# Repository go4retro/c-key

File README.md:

#Commodore PS/2 Keyboard Adapter

##License
Copyright (C) 2004 Jim Brain and RETRO Innovations

These files are free designs; you can redistribute them and/or modify
them under the terms of the GNU General Public License, version 2 as 
published by the Free Software Foundation.

These files are distributed in the hope that they will be useful,
but WITHOUT ANY WARRANTY; without even the implied warranty of
MERCHANTABILITY or FITNESS FOR A PARTICULAR PURPOSE.  See the
GNU General Public License for more details.

You should have received a copy of the GNU General Public License along
with these files; if not, write to the Free Software Foundation, Inc.,
51 Franklin Street, Fifth Floor, Boston, MA 02110-1301 USA.

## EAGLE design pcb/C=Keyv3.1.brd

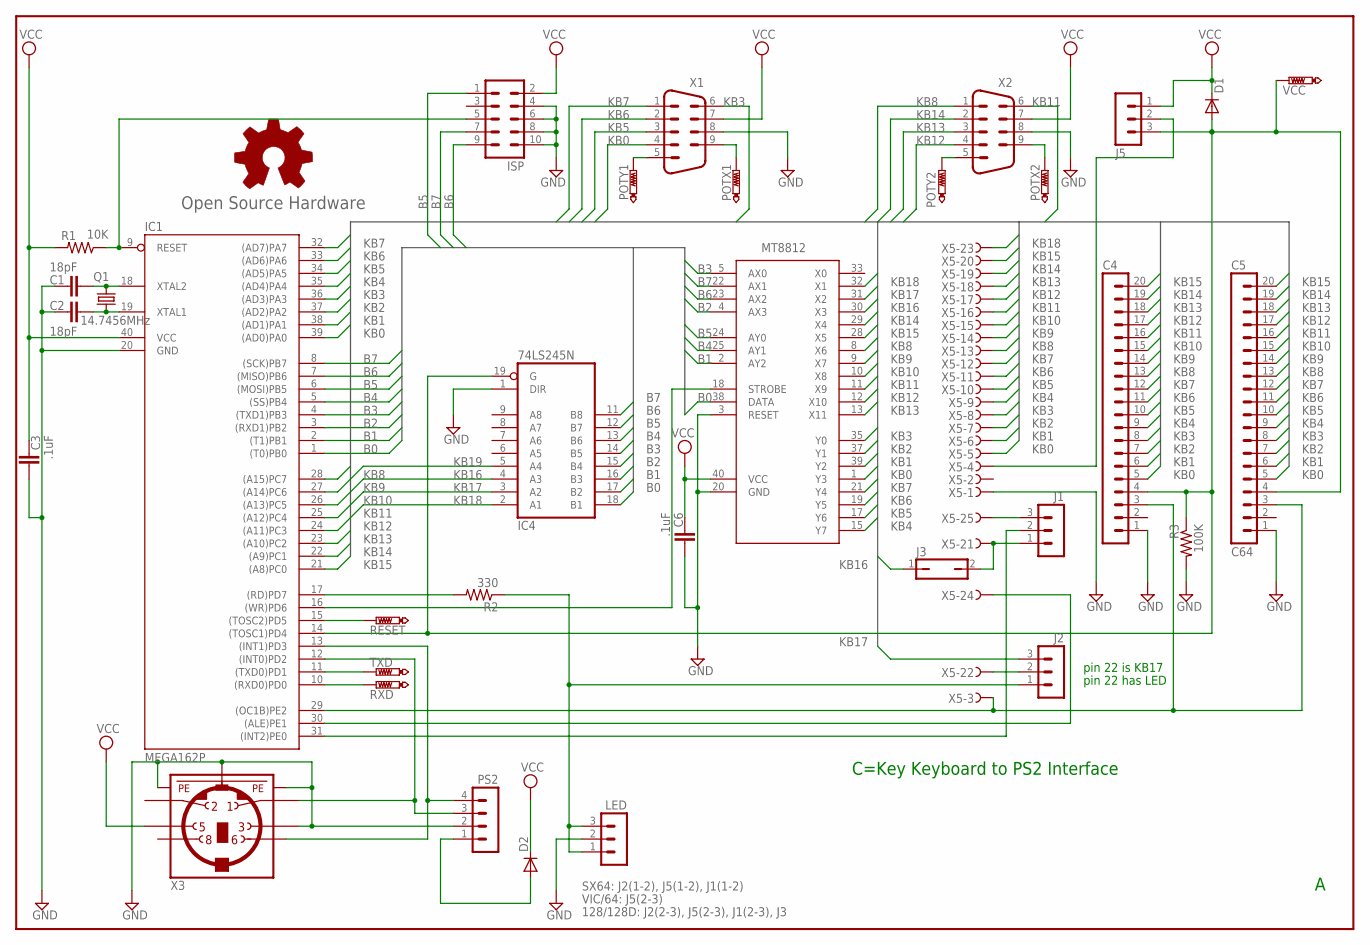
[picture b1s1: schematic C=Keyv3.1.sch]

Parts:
C1, C2: 18pF; C2.5-2
C3, C6: .1uF; C2.5-2
C4: MA20-1
C5: C64; MA20-1
D1, D2: DIODE-DO41-10; DO41-10
GOLD_ORB_SM1: Open Source Hardware; OSHW_5MM
IC1: MEGA162P; DIL40
IC2: MT8812-P; DIP40
IC4: 74LS245N; DIL20
ISP: MA05-2
J1, J2, J5: MA03-1
J3: JP1Q; JP1
LED: MA03-1
POTX1, POTX2: PTR1PAD1-13; P1-13
POTY1, POTY2: PTR1PAD1-13; P1-13
PS2: MA04-1
Q1: 14.7456MHz; HC49U-V
R1: 10K; 0204/5
R2: 330; 0204/5
R3: 100K; 0204V
RESET: PTR1PAD1-13; P1-13
RXD: PTR1PAD1-13; P1-13
TXD: PTR1PAD1-13; P1-13
VCC: PTR1PAD1-13; P1-13
X1, X2: M09HP
X3: MINI_DIN_6; M_DIN6
X5: F25HPS; F25HP

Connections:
B0: IC1.1 ((T0)PB0), IC2.38 (DATA), IC4.18 (B1)
B1: IC1.2 ((T1)PB1), IC2.2 (AY2), IC4.17 (B2)
B2: IC1.3 ((RXD1)PB2), IC2.4 (AX3), IC4.16 (B3)
B3: IC1.4 ((TXD1)PB3), IC2.5 (AX0), IC4.15 (B4)
B4: IC1.5 ((SS)PB4), IC2.25 (AY1), IC4.14 (B5)
B5: IC1.6 ((MOSI)PB5), IC2.24 (AY0), IC4.13 (B6), ISP.1
B6: IC1.7 ((MISO)PB6), IC2.23 (AX2), IC4.12 (B7), ISP.9
B7: IC1.8 ((SCK)PB7), IC2.22 (AX1), IC4.11 (B8), ISP.7
GND: C1.1, C2.1, C3.2, C4.1, C5.1, C6.2, IC1.20 (GND), IC2.3 (RESET), IC2.20 (GND), IC4.1 (DIR), IC4.10 (GND), ISP.4, ISP.6, ISP.8, ISP.10, LED.2, PS2.2, R3.2, X1.8, X2.8, X3.3, X3.SH1 (PE1), X3.SH2 (PE2), X3.SH3 (PE3), X5.1
KB0: C4.5, C5.5, IC1.39 ((AD0)PA0), IC2.1 (Y3), X1.4, X5.5
KB1: C4.6, C5.6, IC1.38 ((AD1)PA1), IC2.39 (Y2), X5.6
KB2: C4.7, C5.7, IC1.37 ((AD2)PA2), IC2.37 (Y1), X5.7
KB3: C4.8, C5.8, IC1.36 ((AD3)PA3), IC2.35 (Y0), X1.6, X5.8
KB4: C4.9, C5.9, IC1.35 ((AD4)PA4), IC2.15 (Y7), X5.9
KB5: C4.10, C5.10, IC1.34 ((AD5)PA5), IC2.17 (Y6), X1.3, X5.10
KB6: C4.11, C5.11, IC1.33 ((AD6)PA6), IC2.19 (Y5), X1.2, X5.11
KB7: C4.12, C5.12, IC1.32 ((AD7)PA7), IC2.21 (Y4), X1.1, X5.12
KB8: C4.13, C5.13, IC1.28 ((A15)PC7), IC2.8 (X6), X2.1, X5.13
KB9: C4.14, C5.14, IC1.27 ((A14)PC6), IC2.9 (X7), X5.14
KB10: C4.15, C5.15, IC1.26 ((A13)PC5), IC2.10 (X8), X5.15
KB11: C4.16, C5.16, IC1.25 ((A12)PC4), IC2.11 (X9), X2.6, X5.16
KB12: C4.17, C5.17, IC1.24 ((A11)PC3), IC2.12 (X10), X2.4, X5.17
KB13: C4.18, C5.18, IC1.23 ((A10)PC2), IC2.13 (X11), X2.3, X5.18
KB14: C4.19, C5.19, IC1.22 ((A9)PC1), IC2.29 (X4), X2.2, X5.19
KB15: C4.20, C5.20, IC1.21 ((A8)PC0), IC2.28 (X5), X5.20
KB16: IC2.30 (X3), IC4.4 (A3), J3.1
KB17: IC2.31 (X2), IC4.3 (A2), J2.3
KB18: IC2.32 (X1), IC4.2 (A1), X5.23
KB19: IC4.5 (A4)
unnamed: D2.A, PS2.1
unnamed: IC1.31 ((INT2)PE0), J1.2
unnamed: J1.3, X5.25
unnamed: J1.1, J3.2, X5.21
unnamed: J2.2, X5.22
unnamed: IC1.9 (RESET), ISP.5, R1.1
unnamed: IC1.15 ((TOSC2)PD5), RESET.1
unnamed: C4.4, C5.4, D1.A, IC1.14 ((TOSC1)PD4), IC4.19 (G), J5.3, R3.1, VCC.1
unnamed: J5.2, X5.4
unnamed: J2.1, LED.1, LED.3, R2.1
unnamed: POTX1.1, X1.9
unnamed: POTX2.1, X2.9
unnamed: POTY2.1, X2.5
unnamed: IC1.16 ((WR)PD6), IC2.18 (STROBE)
unnamed: IC1.10 ((RXD0)PD0), RXD.1
unnamed: IC1.11 ((TXD0)PD1), TXD.1
unnamed: IC1.12 ((INT0)PD2), PS2.3, X3.1
unnamed: IC1.13 ((INT1)PD3), PS2.4, X3.6
unnamed: C4.3, C5.3, IC1.29 ((OC1B)PE2), X5.3
unnamed: IC1.30 ((ALE)PE1), X5.24
unnamed: IC1.17 ((RD)PD7), R2.2
unnamed: C1.2, IC1.18 (XTAL2), Q1.2
unnamed: POTY1.1, X1.5
unnamed: C2.2, IC1.19 (XTAL1), Q1.1
VCC: C3.1, C6.1, D1.C, D2.C, IC1.40 (VCC), IC2.40 (VCC), IC4.20 (VCC), ISP.2, J5.1, R1.2, X1.7, X2.7, X3.5

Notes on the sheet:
C=Key Keyboard to PS2 Interface
pin 22 has LED
pin 22 is KB17
SX64: J2(1-2), J5(1-2), J1(1-2)
128/128D: J2(2-3), J5(2-3), J1(2-3), J3
VIC/64: J5(2-3)

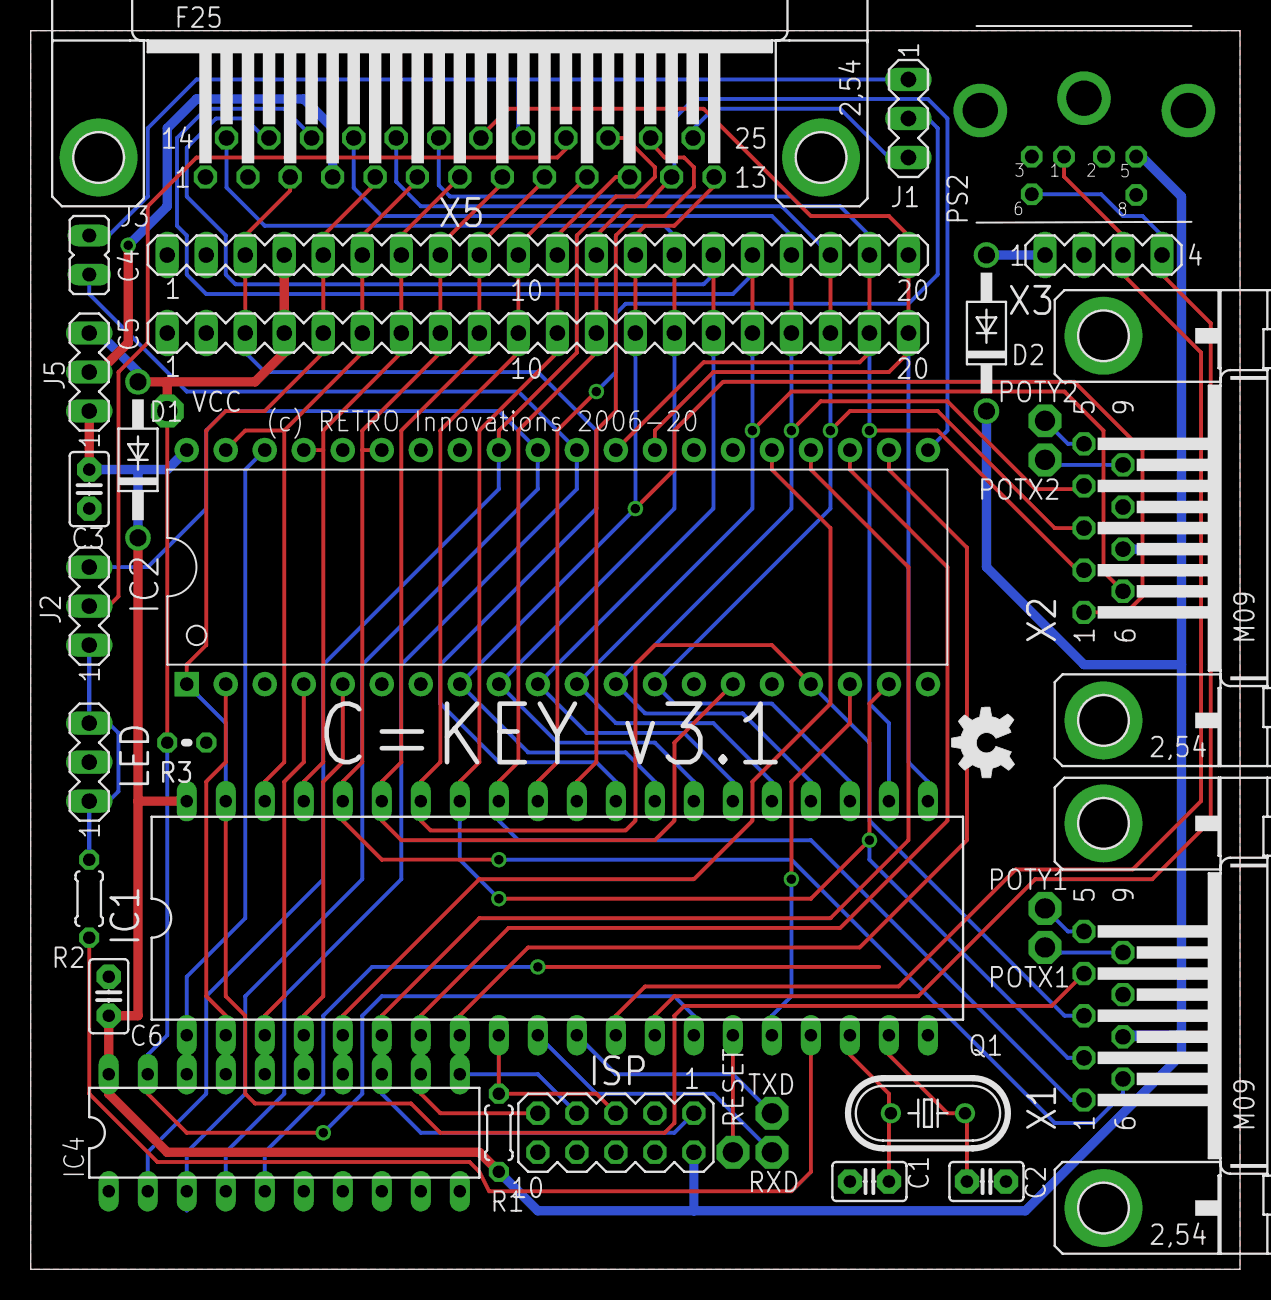
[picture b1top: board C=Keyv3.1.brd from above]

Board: 2 copper layers, 78.7 x 80.6 mm, 35 parts (0 on the bottom side), 53 nets.

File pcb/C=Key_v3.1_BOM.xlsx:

Part | Value | Device | Quantity | Description | Source
C1,C2 | 18pF | C2.5/2 | 2 | CAPACITOR | https://www.digikey.com/en/products/detail/vishay-beyschlag-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
C3,C6 | .1uF | C2.5/2 | 2 | CAPACITOR | https://www.digikey.com/en/products/detail/vishay-beyschlag-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
C4 |  | MA20-1 | 1 | PIN HEADER | https://www.digikey.com/en/products/detail/sullins-connector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
C5 | C64 | MA20-1 | 1 | PIN HEADER | https://www.digikey.com/en/products/detail/sullins-connector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
D1,D2 |  | DIODE-DO41-10 | 2 | DIODE | https://www.digikey.com/en/products/detail/micro-commercial-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
IC1 | MEGA162P | MEGA161P | 1 | MICROCONTROLLER | https://www.digikey.com/en/products/detail/microchip-technol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
IC2 | MT8812-P | MT8812-P | 1
IC4 | 74LS245N | 74LS245N | 1 | Octal BUS TRANSCEIVER, 3-state | https://www.digikey.com/en/products/detail/texas-instruments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
J1,J2,J5,LED |  | MA03-1 | 4 | PIN HEADER | https://www.digikey.com/en/products/detail/adam-tech/PH1-12-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
J3 |  | JP1Q | 1 | JUMPER | https://www.digikey.com/en/products/detail/adam-tech/PH1-02-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
PS2 |  | MA04-1 | 1 | PIN HEADER | https://www.digikey.com/en/products/detail/adam-tech/PH1-04-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
Q1 | 14.7456MHz | CRYTALHC49U-V | 1 | CRYSTAL | https://www.digikey.com/en/products/detail/abracon-llc/ABL-1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
R1 | 10K | R-US_0204/5 | 1 | RESISTOR, American symbol | https://www.digikey.com/en/products/detail/stackpole-electro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
R2 | 330 | R-US_0204/5 | 1 | RESISTOR, American symbol | https://www.digikey.com/en/products/detail/stackpole-electro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
R3 | 100K | R-US_0204/2V | 1 | RESISTOR, American symbol | https://www.digikey.com/en/products/detail/stackpole-electro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
X1,X2 |  | M09HP | 2 | SUB-D | https://www.digikey.com/en/products/detail/assmann-wsw-compo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
X3 |  | MINI_DIN_6 | 1 | MINI_DIN_6 | https://www.digikey.com/en/products/detail/adam-tech/MDJ-006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
X5 |  | F25HPS | 1 | SUB-D | https://www.digikey.com/en/products/detail/amphenol-icc-fci/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

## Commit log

2007-02-05 Initial import.
2007-02-05 Initial code for PC -> 64 direction
2007-02-05 Switch to MEGA162 and merge directions
2007-04-08 In order to more closely approximate the joystick electrical connection on the 64/128, changed the code to support reading the joysticks on the actual KB row and col pins. As a result, had to redo th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
    Also, changed some includes to fix case issues.
2007-04-13 Created new PCB using correct C128/128 kb connector, and will be easier to place in 64/128 units. As well, laid out joysticks to coincide with placement on real 64/128
2007-05-15 o Modified code to work with v3 board o Fixed init code in switch.c (setting DDR and then reading too fast caused false readings) o Fixed issue in PS2 GET DEVICE ID command handling o Set LEDs to HI/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
2007-12-17 Added code to generalize the MODE pin for v2 and v3 designs.
2007-12-17 Fixed mnemonic on FLAG
2007-12-17 Minor LED init fix
2007-12-18 Fixed prototype for SW_send
2007-12-18 Fixed Ctrl-Alt-Del functionality
2007-12-18 Added jumper for SX64 KB operation and fixed diode drill sizes
2007-12-18 Finished CTRL/ALT/DEL support and started adding config support in host mode.
2007-12-19 Added configuration code to Host mode, added EEPROM saving, and rewrote LED routines
2007-12-25 More code cleanup, and more to do.
2008-01-07 CBM KB -> PS2 bugfixes and code cleanup.
2008-08-06 Last minute fixes.
2008-08-07 New Makefile
2008-08-07 Save reference materials
2008-08-07 Added doc directory
2008-08-07 Cleanup
2008-08-07 Small tweaks for production board layout
2008-08-07 Switch to better CPU define in source files
2008-08-07 Migrated to better uart code
2008-08-07 Add config file and move eeprom code to separate file
2008-08-07 Get rid of LST file
2008-08-07 Moved some items to config.h and removed last items from util.h
2008-08-07 More kb code cleanup
2008-08-08 Final tweaks to kb driver
2008-08-08 Cleanup of uart driver
2008-08-08 cleanup main
2011-06-07 General cleanup of code
2012-03-12 Fixed PS/2 routines to PS/2 KB LED commands work Merged in uart code from PS2Encoder and fixed some compilation options.
    Jim
2012-03-12 Fixed PS/2 routines to PS/2 KB LED commands work Merged in uart code from C=Key and fixed some compilation options.
    Jim
2012-03-12 Fixed copyright
2012-03-12 old config
2013-07-09 PS/2 code tweaks code cleanup GCC PROGMEM mods
2013-11-13 Removing old M16 target
2014-03-16 Minor fixes and Makefile tweaks
2014-03-16 Missed an old M16 target item
2018-08-03 General cleanup for git
2018-10-21 Fix case statement warning about implicit fallthrough.
2020-10-17 A few minor changes
    * Removed useless joystick ground strap on pcb
    * Don't turn on 40/80 by default
    * Add in BOM
2020-10-29 Fix symbolic mapping issues, clean up obj files, and update Makefile
2021-03-06 Use full swing crystal setting in fuses
2025-06-07 Fix masking issue with sw_putc (found by tutigit)
